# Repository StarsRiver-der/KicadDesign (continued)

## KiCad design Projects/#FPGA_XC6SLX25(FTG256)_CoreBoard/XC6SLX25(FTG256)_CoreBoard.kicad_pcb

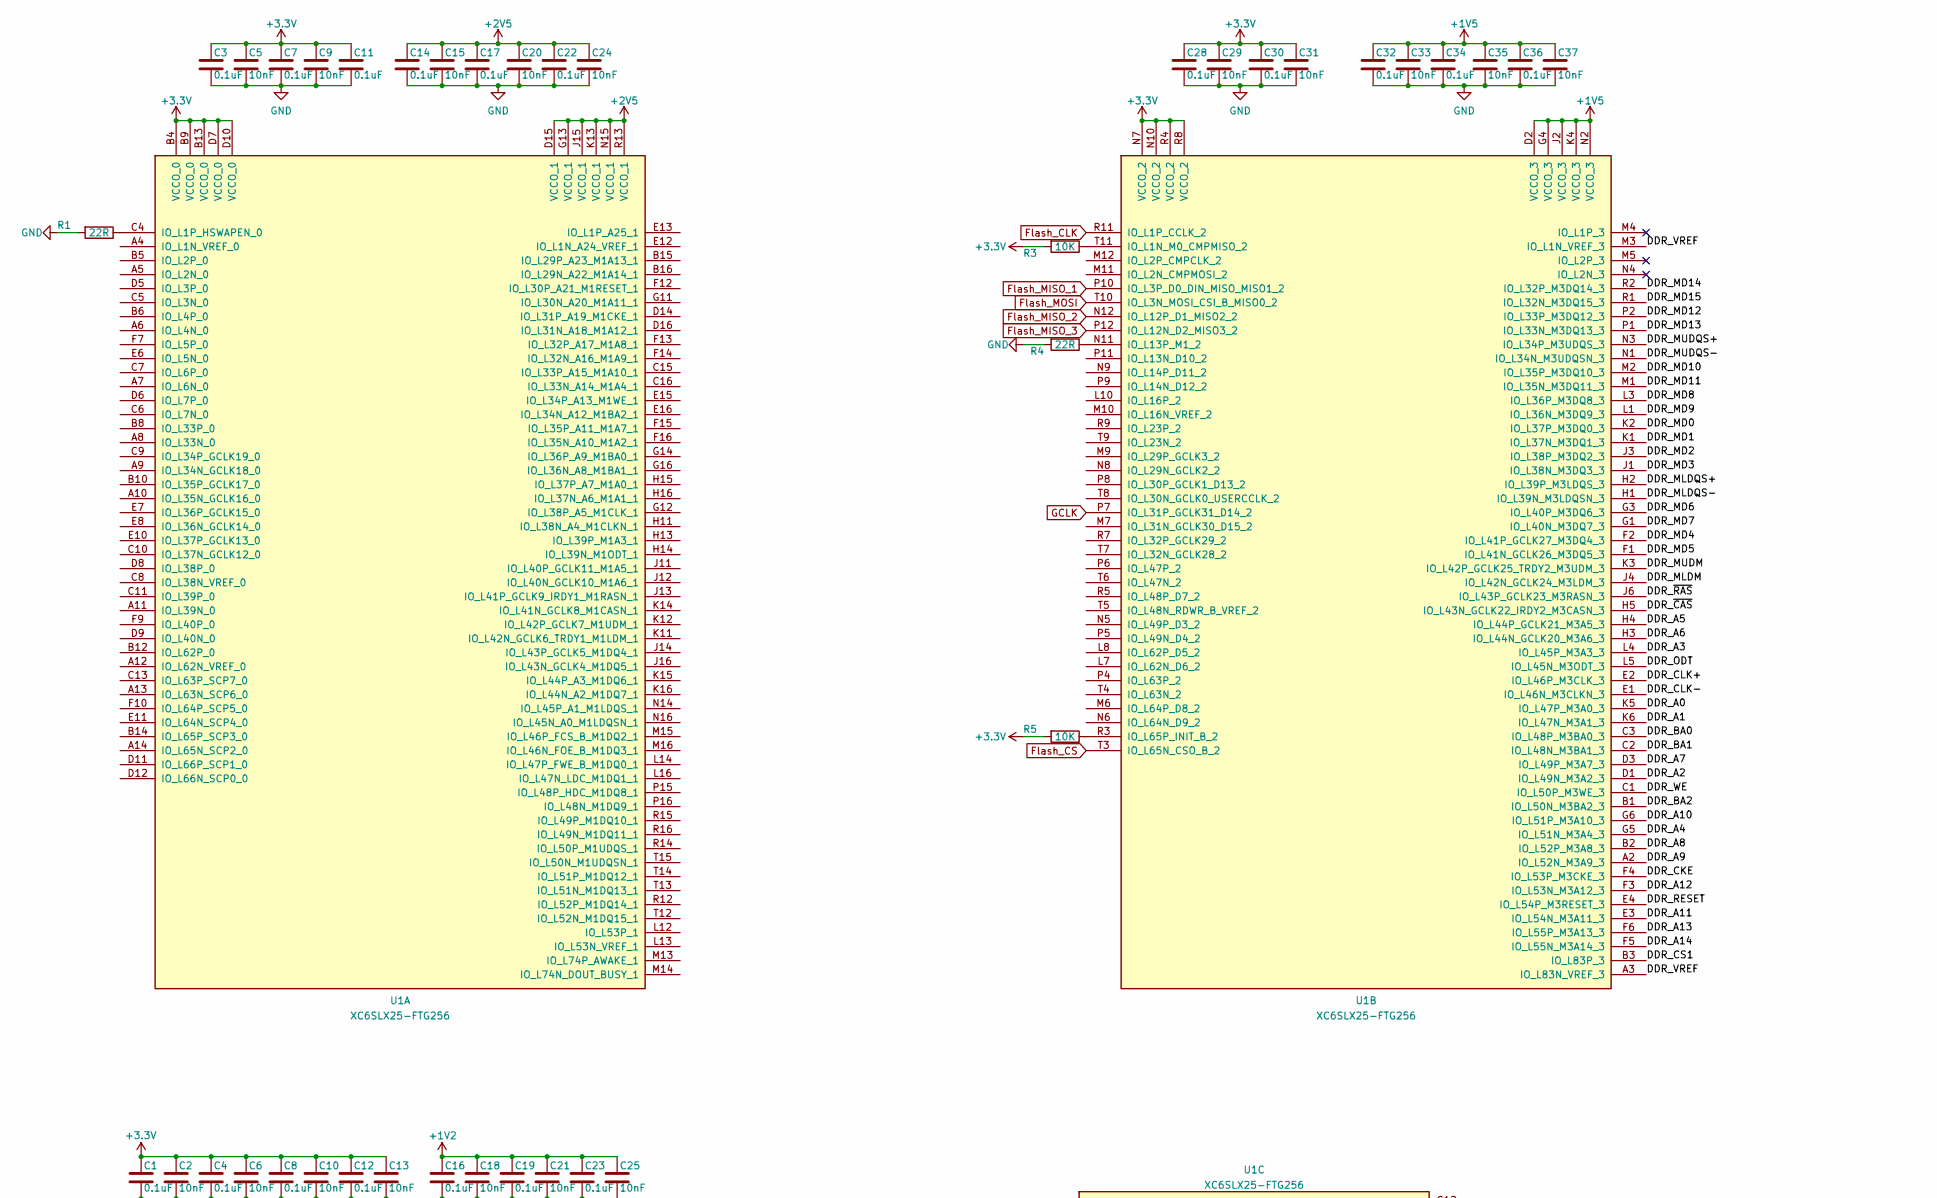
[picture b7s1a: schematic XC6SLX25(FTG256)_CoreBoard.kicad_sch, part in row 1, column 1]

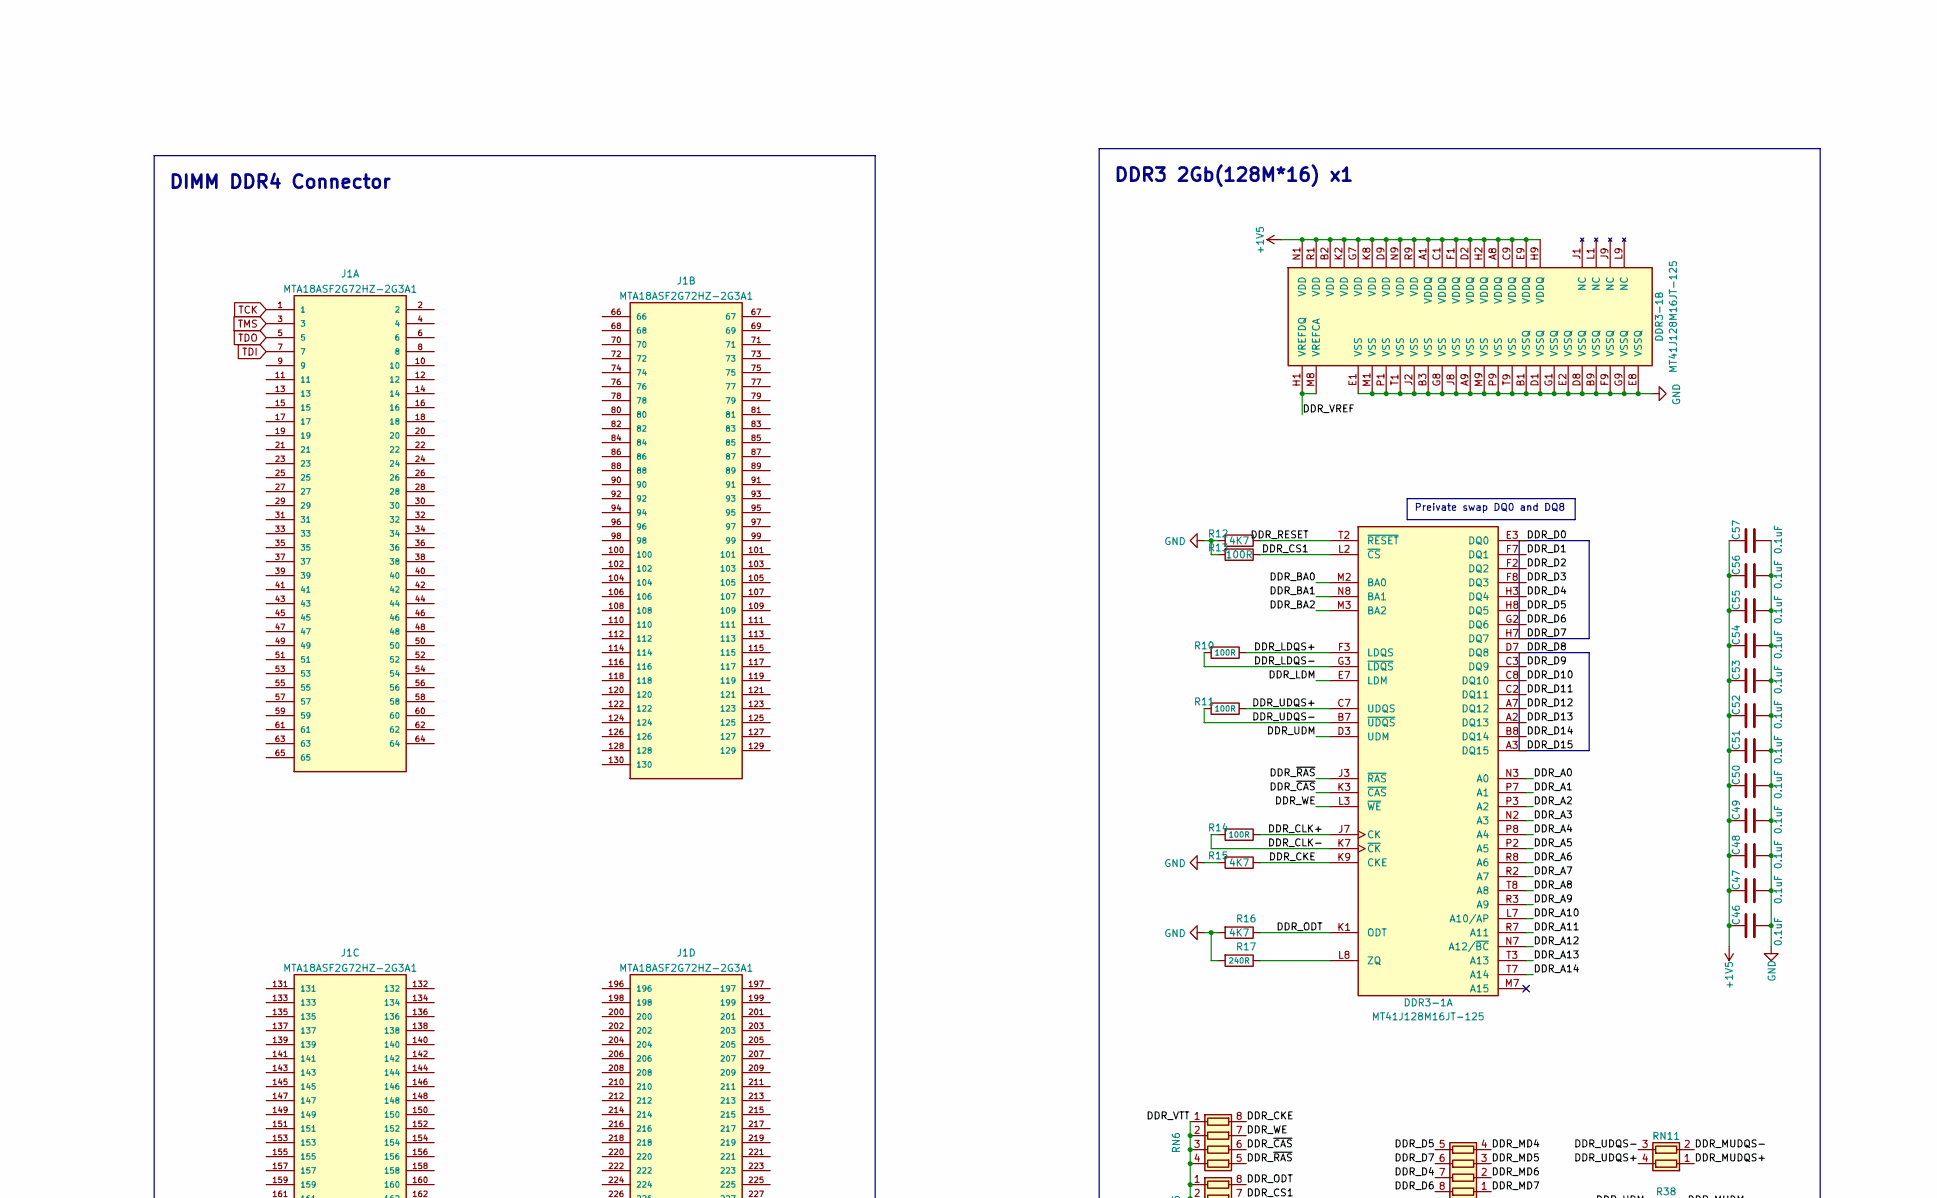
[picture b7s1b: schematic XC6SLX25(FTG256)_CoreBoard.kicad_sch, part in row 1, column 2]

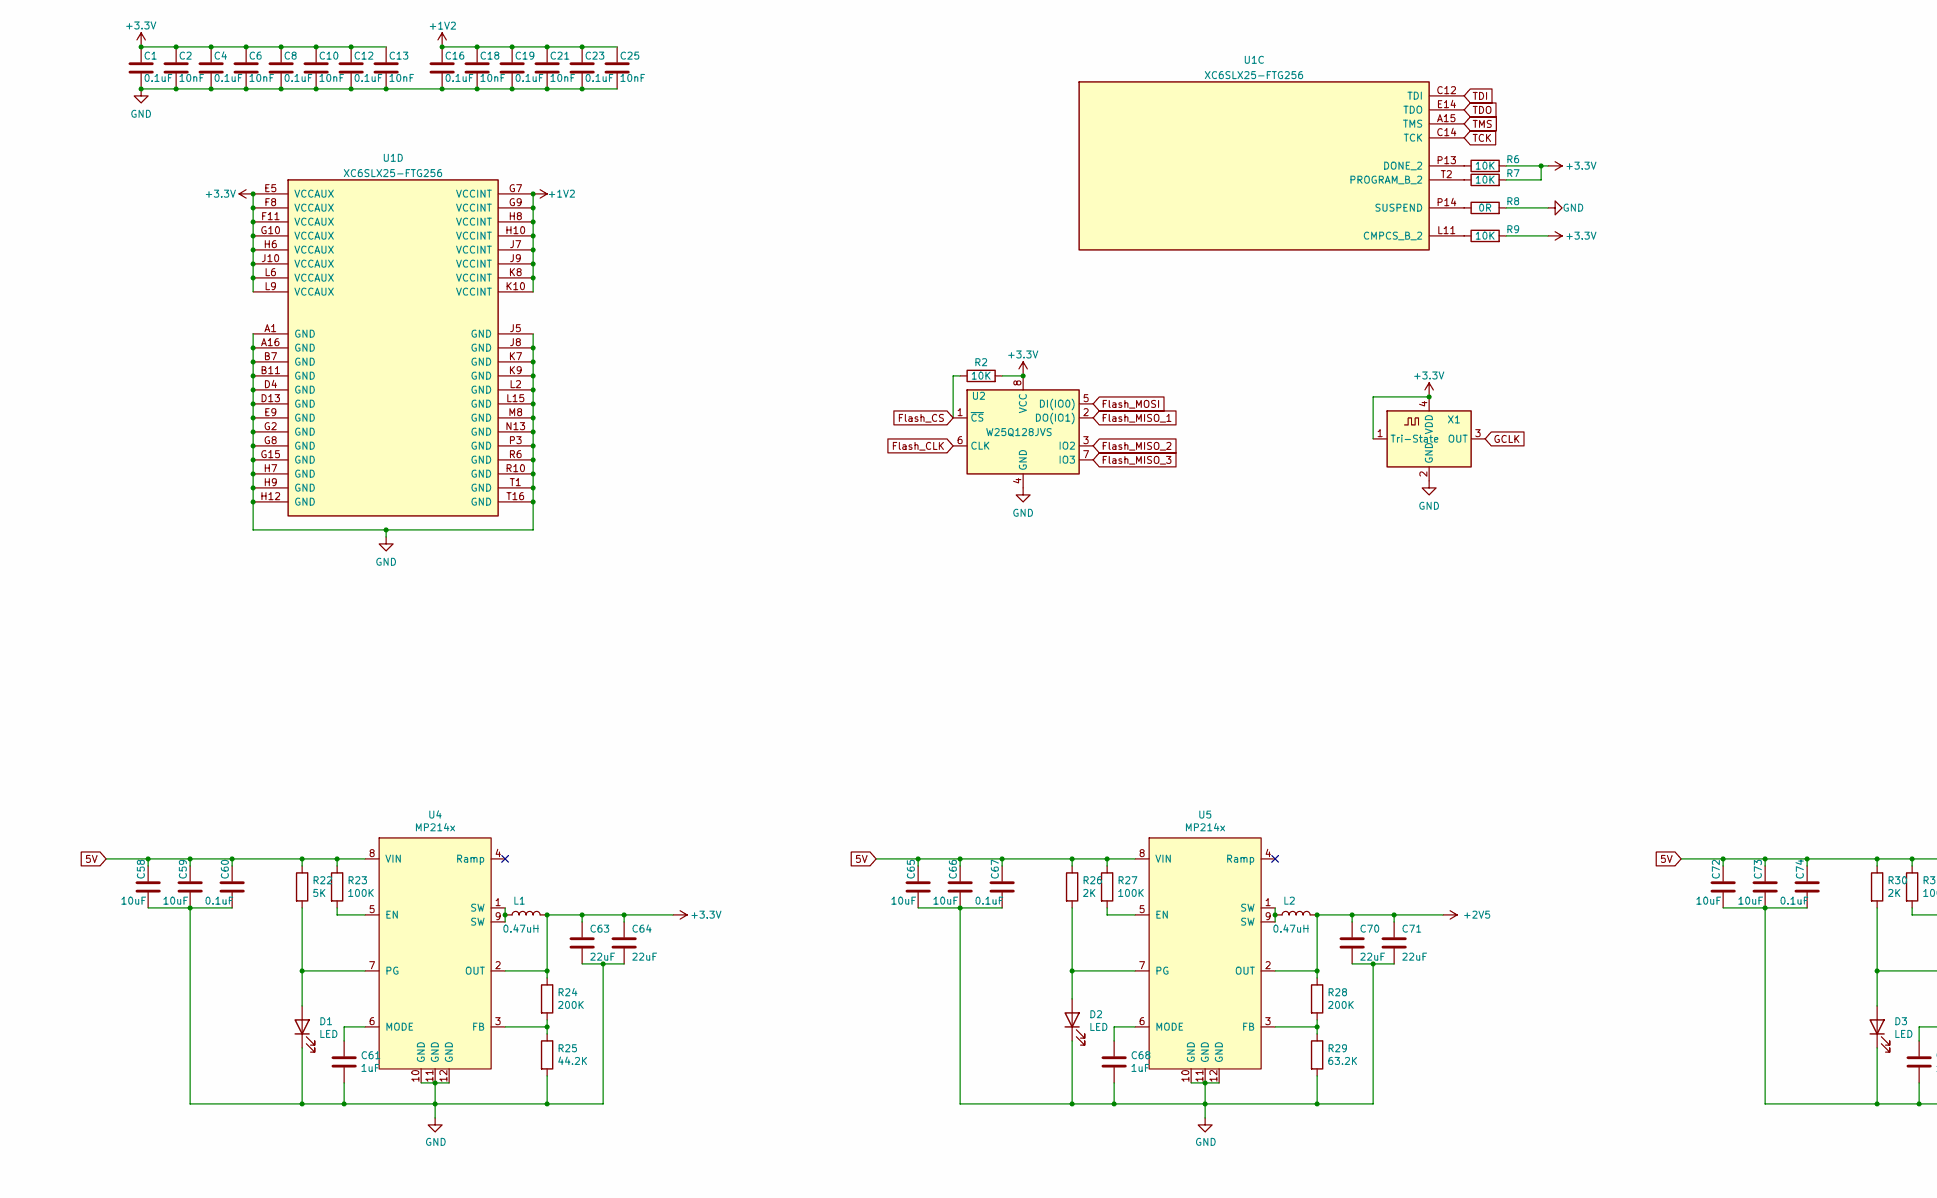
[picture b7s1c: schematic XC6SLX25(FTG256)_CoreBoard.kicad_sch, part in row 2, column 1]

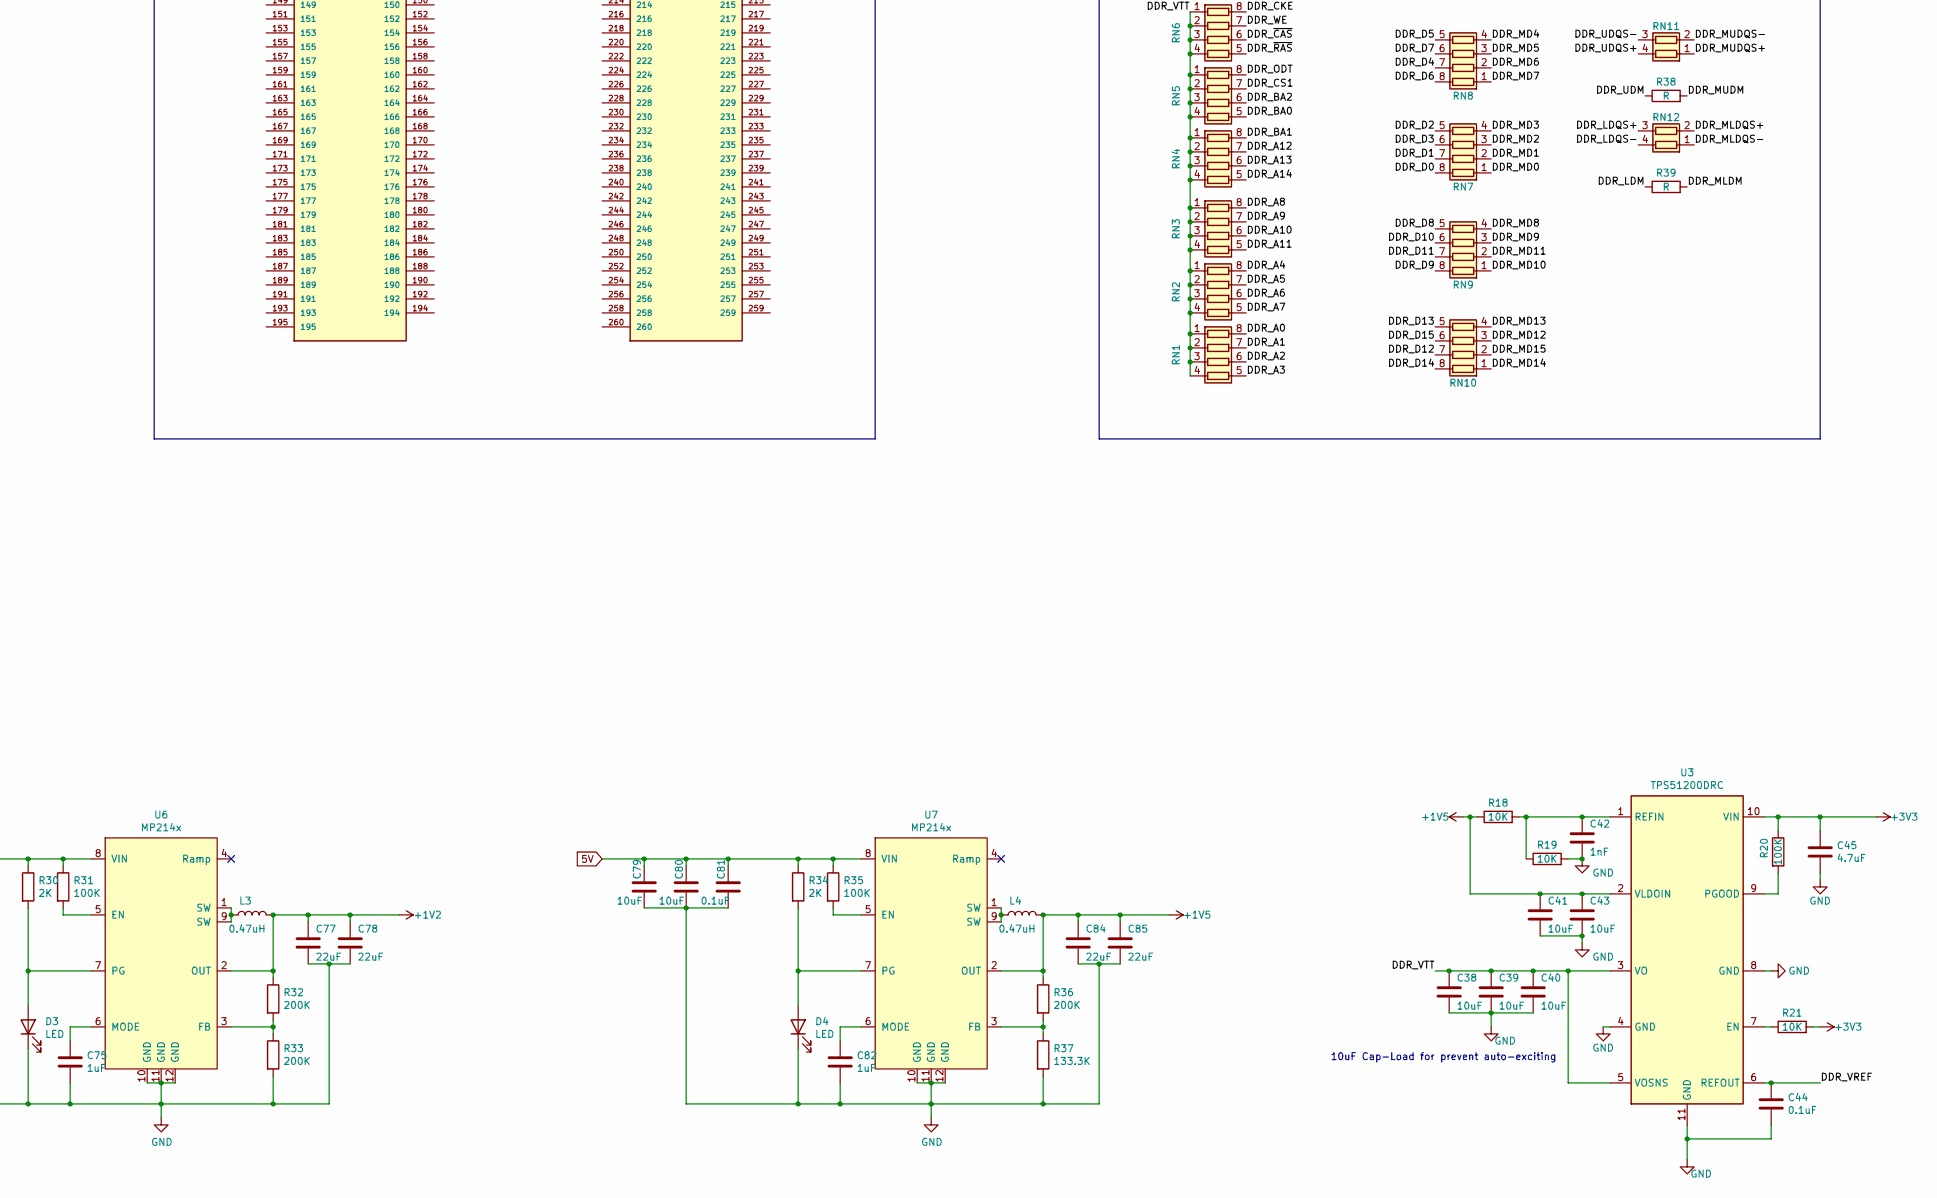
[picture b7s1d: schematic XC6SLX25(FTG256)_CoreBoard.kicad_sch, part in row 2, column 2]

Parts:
C1, C3, C4, C7, C8, C11, C12, C14, C17, C22, C28, C30, C32, C34, C36, C44, C46, C47, C48, C49, C50, C51, C52, C53, C54, C55, C56, C57, C60, C67, C74, C81: 0.1uF; C_0402_1005Metric
C2, C5, C6, C9, C10, C13, C15, C20, C24, C29, C31, C33, C35, C37: 10nF; C_0402_1005Metric
C16, C19, C23: 0.1uF; C_0201_0603Metric
C18, C21, C25: 10nF; C_0201_0603Metric
C38, C39, C40, C41, C43, C58, C59, C65, C66, C72, C73, C79, C80: 10uF; C_0402_1005Metric
C42: 1nF; C_0402_1005Metric
C45: 4.7uF; C_0402_1005Metric
C61, C68, C75, C82: 1uF; C_0402_1005Metric
C63, C64, C70, C71, C77, C78, C84, C85: 22uF; C_0603_1608Metric
D1, D2, D3, D4: LED; LED_0402_1005Metric
DDR3-1: MT41J128M16JT-125; DDR3-BGA96
J1: MTA18ASF2G72HZ-2G3A1; SO-DIMM-DDR4-pcb
L1, L2, L3, L4: 0.47uH; L_Taiyo-Yuden_NR-30xx
R1, R4: 22R; R_0402_1005Metric
R2, R3, R5, R6, R7, R9, R18, R19, R21: 10K; R_0402_1005Metric
R8: 0R; R_0402_1005Metric
R10, R11, R13, R14: 100R; R_0402_1005Metric
R12, R15, R16: 4K7; R_0402_1005Metric
R17: 240R; R_0402_1005Metric
R20, R23, R27, R31, R35: 100K; R_0402_1005Metric
R22: 5K; R_0402_1005Metric
R24, R28, R32, R33, R36: 200K; R_0402_1005Metric
R25: 44.2K; R_0402_1005Metric
R26, R30, R34: 2K; R_0402_1005Metric
R29: 63.2K; R_0402_1005Metric
R37: 133.3K; R_0402_1005Metric
R38, R39: R; R_0402_1005Metric
RN1, RN2, RN3, RN4, RN5, RN6, RN7, RN8, RN9, RN10: R_Pack04; R_Array_Concave_4x0402
RN11, RN12: R_Pack02; R_Array_Convex_2x0402
U1: XC6SLX25-FTG256; Xilinx_FTG256
U2: W25Q128JVS; SOIC-8_5.23x5.23mm_P1.27mm
U3: TPS51200DRC; VSON-10-1EP_3x3mm_P0.5mm_EP1.65x2.4mm
U4, U5, U6, U7: MP214x; MP2145
X1: ECS-2520MV-xxx-xx; Oscillator_SMD_ECS_2520MV-xxx-xx-4Pin_2.5x2.0mm

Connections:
5V: C58.1, C59.1, C60.1, C65.1, C66.1, C67.1, C72.1, C73.1, C74.1, C79.1, C80.1, C81.1, R22.1, R23.1, R26.1, R27.1, R30.1, R31.1, R34.1, R35.1, U4.8 (VIN), U5.8 (VIN), U6.8 (VIN), U7.8 (VIN)
+1V2: C16.1, C18.1, C19.1, C21.1, C23.1, C25.1, C77.1, C78.1, L3.2, R32.1, U1.G7 (VCCINT), U1.G9 (VCCINT), U1.H8 (VCCINT), U1.H10 (VCCINT), U1.J7 (VCCINT), U1.J9 (VCCINT), U1.K8 (VCCINT), U1.K10 (VCCINT), U6.2 (OUT)
+1V5: C32.1, C33.1, C34.1, C35.1, C36.1, C37.1, C41.1, C43.1, C46.1, C47.1, C48.1, C49.1, C50.1, C51.1, C52.1, C53.1, C54.1, C55.1, C56.1, C57.1, C84.1, C85.1, DDR3-1.A1 (VDDQ), DDR3-1.A8 (VDDQ), DDR3-1.B2 (VDD), DDR3-1.C1 (VDDQ), DDR3-1.C9 (VDDQ), DDR3-1.D2 (VDDQ), DDR3-1.D9 (VDD), DDR3-1.E9 (VDDQ), DDR3-1.F1 (VDDQ), DDR3-1.G7 (VDD), DDR3-1.H2 (VDDQ), DDR3-1.H9 (VDDQ), DDR3-1.K2 (VDD), DDR3-1.K8 (VDD), DDR3-1.N1 (VDD), DDR3-1.N9 (VDD), DDR3-1.R1 (VDD), DDR3-1.R9 (VDD), L4.2, R18.1, R36.1, U1.D2 (VCCO_3), U1.G4 (VCCO_3), U1.J2 (VCCO_3), U1.K4 (VCCO_3), U1.N2 (VCCO_3), U3.2 (VLDOIN), U7.2 (OUT)
+2V5: C14.1, C15.1, C17.1, C20.1, C22.1, C24.1, C70.1, C71.1, L2.2, R28.1, U1.D15 (VCCO_1), U1.G13 (VCCO_1), U1.J15 (VCCO_1), U1.K13 (VCCO_1), U1.N15 (VCCO_1), U1.R13 (VCCO_1), U5.2 (OUT)
/DDR_A0: DDR3-1.N3 (A0), RN1.8 (R1.2), U1.K5 (IO_L47P_M3A0_3)
/DDR_A1: DDR3-1.P7 (A1), RN1.7 (R2.2), U1.K6 (IO_L47N_M3A1_3)
/DDR_A2: DDR3-1.P3 (A2), RN1.6 (R3.2), U1.D1 (IO_L49N_M3A2_3)
/DDR_A3: DDR3-1.N2 (A3), RN1.5 (R4.2), U1.L4 (IO_L45P_M3A3_3)
/DDR_A4: DDR3-1.P8 (A4), RN2.8 (R1.2), U1.G5 (IO_L51N_M3A4_3)
/DDR_A5: DDR3-1.P2 (A5), RN2.7 (R2.2), U1.H4 (IO_L44P_GCLK21_M3A5_3)
/DDR_A6: DDR3-1.R8 (A6), RN2.6 (R3.2), U1.H3 (IO_L44N_GCLK20_M3A6_3)
/DDR_A7: DDR3-1.R2 (A7), RN2.5 (R4.2), U1.D3 (IO_L49P_M3A7_3)
/DDR_A8: DDR3-1.T8 (A8), RN3.8 (R1.2), U1.B2 (IO_L52P_M3A8_3)
/DDR_A9: DDR3-1.R3 (A9), RN3.7 (R2.2), U1.A2 (IO_L52N_M3A9_3)
/DDR_A10: DDR3-1.L7 (A10/AP), RN3.6 (R3.2), U1.G6 (IO_L51P_M3A10_3)
/DDR_A11: DDR3-1.R7 (A11), RN3.5 (R4.2), U1.E3 (IO_L54N_M3A11_3)
/DDR_A12: DDR3-1.N7 (A12/~BC), RN4.7 (R2.2), U1.F3 (IO_L53N_M3A12_3)
/DDR_A13: DDR3-1.T3 (A13), RN4.6 (R3.2), U1.F6 (IO_L55P_M3A13_3)
/DDR_A14: DDR3-1.T7 (A14), RN4.5 (R4.2), U1.F5 (IO_L55N_M3A14_3)
/DDR_BA0: DDR3-1.M2 (BA0), RN5.5 (R4.2), U1.C3 (IO_L48P_M3BA0_3)
/DDR_BA1: DDR3-1.N8 (BA1), RN4.8 (R1.2), U1.C2 (IO_L48N_M3BA1_3)
/DDR_BA2: DDR3-1.M3 (BA2), RN5.6 (R3.2), U1.B1 (IO_L50N_M3BA2_3)
/DDR_CKE: DDR3-1.K9 (CKE), R15.1, RN6.8 (R1.2), U1.F4 (IO_L53P_M3CKE_3)
/DDR_CLK+: DDR3-1.J7 (CK), R14.1, U1.E2 (IO_L46P_M3CLK_3)
/DDR_CLK-: DDR3-1.K7 (~CK), R14.2, U1.E1 (IO_L46N_M3CLKN_3)
/DDR_CS1: DDR3-1.L2 (~CS), R13.1, RN5.7 (R2.2), U1.B3 (IO_L83P_3)
/DDR_D0: DDR3-1.E3 (DQ0), RN7.8 (R1.2)
/DDR_D1: DDR3-1.F7 (DQ1), RN7.7 (R2.2)
/DDR_D2: DDR3-1.F2 (DQ2), RN7.5 (R4.2)
/DDR_D3: DDR3-1.F8 (DQ3), RN7.6 (R3.2)
/DDR_D4: DDR3-1.H3 (DQ4), RN8.7 (R2.2)
/DDR_D5: DDR3-1.H8 (DQ5), RN8.5 (R4.2)
/DDR_D6: DDR3-1.G2 (DQ6), RN8.8 (R1.2)
/DDR_D7: DDR3-1.H7 (DQ7), RN8.6 (R3.2)
/DDR_D8: DDR3-1.D7 (DQ8), RN9.5 (R4.2)
/DDR_D9: DDR3-1.C3 (DQ9), RN9.8 (R1.2)
/DDR_D10: DDR3-1.C8 (DQ10), RN9.6 (R3.2)
/DDR_D11: DDR3-1.C2 (DQ11), RN9.7 (R2.2)
/DDR_D12: DDR3-1.A7 (DQ12), RN10.7 (R2.2)
/DDR_D13: DDR3-1.A2 (DQ13), RN10.5 (R4.2)
/DDR_D14: DDR3-1.B8 (DQ14), RN10.8 (R1.2)
/DDR_D15: DDR3-1.A3 (DQ15), RN10.6 (R3.2)
/DDR_LDM: DDR3-1.E7 (LDM), R39.1
/DDR_LDQS+: DDR3-1.F3 (LDQS), R10.1, RN12.3 (R2.2)
/DDR_LDQS-: DDR3-1.G3 (~LDQS), R10.2, RN12.4 (R1.2)
/DDR_MD0: RN7.1 (R1.1), U1.K2 (IO_L37P_M3DQ0_3)
/DDR_MD1: RN7.2 (R2.1), U1.K1 (IO_L37N_M3DQ1_3)
/DDR_MD2: RN7.3 (R3.1), U1.J3 (IO_L38P_M3DQ2_3)
/DDR_MD3: RN7.4 (R4.1), U1.J1 (IO_L38N_M3DQ3_3)
/DDR_MD4: RN8.4 (R4.1), U1.F2 (IO_L41P_GCLK27_M3DQ4_3)
/DDR_MD5: RN8.3 (R3.1), U1.F1 (IO_L41N_GCLK26_M3DQ5_3)
/DDR_MD6: RN8.2 (R2.1), U1.G3 (IO_L40P_M3DQ6_3)
/DDR_MD7: RN8.1 (R1.1), U1.G1 (IO_L40N_M3DQ7_3)
/DDR_MD8: RN9.4 (R4.1), U1.L3 (IO_L36P_M3DQ8_3)
/DDR_MD9: RN9.3 (R3.1), U1.L1 (IO_L36N_M3DQ9_3)
/DDR_MD10: RN9.1 (R1.1), U1.M2 (IO_L35P_M3DQ10_3)
/DDR_MD11: RN9.2 (R2.1), U1.M1 (IO_L35N_M3DQ11_3)
/DDR_MD12: RN10.3 (R3.1), U1.P2 (IO_L33P_M3DQ12_3)
/DDR_MD13: RN10.4 (R4.1), U1.P1 (IO_L33N_M3DQ13_3)
/DDR_MD14: RN10.1 (R1.1), U1.R2 (IO_L32P_M3DQ14_3)
/DDR_MD15: RN10.2 (R2.1), U1.R1 (IO_L32N_M3DQ15_3)
/DDR_MLDM: R39.2, U1.J4 (IO_L42N_GCLK24_M3LDM_3)
/DDR_MLDQS+: RN12.2 (R2.1), U1.H2 (IO_L39P_M3LDQS_3)
/DDR_MLDQS-: RN12.1 (R1.1), U1.H1 (IO_L39N_M3LDQSN_3)
/DDR_MUDM: R38.2, U1.K3 (IO_L42P_GCLK25_TRDY2_M3UDM_3)
/DDR_MUDQS+: RN11.1 (R1.1), U1.N3 (IO_L34P_M3UDQS_3)
/DDR_MUDQS-: RN11.2 (R2.1), U1.N1 (IO_L34N_M3UDQSN_3)
/DDR_ODT: DDR3-1.K1 (ODT), R16.1, RN5.8 (R1.2), U1.L5 (IO_L45N_M3ODT_3)
/DDR_RESET: DDR3-1.T2 (~RESET), R12.1, U1.E4 (IO_L54P_M3RESET_3)
/DDR_UDM: DDR3-1.D3 (UDM), R38.1
/DDR_UDQS+: DDR3-1.C7 (UDQS), R11.1, RN11.4 (R1.2)
/DDR_UDQS-: DDR3-1.B7 (~UDQS), R11.2, RN11.3 (R2.2)
/DDR_VREF: C44.1, DDR3-1.H1 (VREFDQ), DDR3-1.M8 (VREFCA), U1.A3 (IO_L83N_VREF_3), U1.M3 (IO_L1N_VREF_3), U3.6 (REFOUT)
/DDR_VTT: C38.1, C39.1, C40.1, RN1.1 (R1.1), RN1.2 (R2.1), RN1.3 (R3.1), RN1.4 (R4.1), RN2.1 (R1.1), RN2.2 (R2.1), RN2.3 (R3.1), RN2.4 (R4.1), RN3.1 (R1.1), RN3.2 (R2.1), RN3.3 (R3.1), RN3.4 (R4.1), RN4.1 (R1.1), RN4.2 (R2.1), RN4.3 (R3.1), RN4.4 (R4.1), RN5.1 (R1.1), RN5.2 (R2.1), RN5.3 (R3.1), RN5.4 (R4.1), RN6.1 (R1.1), RN6.2 (R2.1), RN6.3 (R3.1), RN6.4 (R4.1), U3.3 (VO), U3.5 (VOSNS)
/DDR_WE: DDR3-1.L3 (~WE), RN6.7 (R2.2), U1.C1 (IO_L50P_M3WE_3)
/DDR_~CAS: DDR3-1.K3 (~CAS), RN6.6 (R3.2), U1.H5 (IO_L43N_GCLK22_IRDY2_M3CASN_3)
/DDR_~RAS: DDR3-1.J3 (~RAS), RN6.5 (R4.2), U1.J6 (IO_L43P_GCLK23_M3RASN_3)
Flash_CLK: U1.R11 (IO_L1P_CCLK_2), U2.6 (CLK)
Flash_CS: R2.1, U1.T3 (IO_L65N_CSO_B_2), U2.1 (~CS)
Flash_MISO_1: U1.P10 (IO_L3P_D0_DIN_MISO_MISO1_2), U2.2 (DO(IO1))
Flash_MISO_2: U1.N12 (IO_L12P_D1_MISO2_2), U2.3 (IO2)
Flash_MISO_3: U1.P12 (IO_L12N_D2_MISO3_2), U2.7 (IO3)
Flash_MOSI: U1.T10 (IO_L3N_MOSI_CSI_B_MISO0_2), U2.5 (DI(IO0))
GCLK: U1.P7 (IO_L31P_GCLK31_D14_2), X1.3 (OUT)
GND: C1.2, C2.2, C3.2, C4.2, C5.2, C6.2, C7.2, C8.2, C9.2, C10.2, C11.2, C12.2, C13.2, C14.2, C15.2, C16.2, C17.2, C18.2, C19.2, C20.2, C21.2, C22.2, C23.2, C24.2, C25.2, C28.2, C29.2, C30.2, C31.2, C32.2, C33.2, C34.2, C35.2, C36.2, C37.2, C38.2, C39.2, C40.2, C41.2, C42.2, C43.2, C44.2, C45.2, C46.2, C47.2, C48.2, C49.2, C50.2, C51.2, C52.2, C53.2, C54.2, C55.2, C56.2, C57.2, C58.2, C59.2, C60.2, C61.2, C63.2, C64.2, C65.2, C66.2, C67.2, C68.2, C70.2, C71.2, C72.2, C73.2, C74.2, C75.2, C77.2, C78.2, C79.2, C80.2, C81.2, C82.2, C84.2, C85.2, D1.1 (K), D2.1 (K), D3.1 (K), D4.1 (K), DDR3-1.A9 (VSS), DDR3-1.B1 (VSSQ), DDR3-1.B3 (VSS), DDR3-1.B9 (VSSQ), DDR3-1.D1 (VSSQ), DDR3-1.D8 (VSSQ), DDR3-1.E1 (VSS), DDR3-1.E2 (VSSQ), DDR3-1.E8 (VSSQ), DDR3-1.F9 (VSSQ), DDR3-1.G1 (VSSQ), DDR3-1.G8 (VSS), DDR3-1.G9 (VSSQ), DDR3-1.J2 (VSS), DDR3-1.J8 (VSS), DDR3-1.M1 (VSS), DDR3-1.M9 (VSS), DDR3-1.P1 (VSS), DDR3-1.P9 (VSS), DDR3-1.T1 (VSS), DDR3-1.T9 (VSS), R1.2, R4.2, R8.2, R12.2, R13.2, R15.2, R16.2, R17.2, R19.2, R25.2, R29.2, R33.2, R37.2, U1.A1 (GND), U1.A16 (GND), U1.B7 (GND), U1.B11 (GND), U1.D4 (GND), U1.D13 (GND), U1.E9 (GND), U1.G2 (GND), U1.G8 (GND), U1.G15 (GND), U1.H7 (GND), U1.H9 (GND), U1.H12 (GND), U1.J5 (GND), U1.J8 (GND), U1.K7 (GND), U1.K9 (GND), U1.L2 (GND), U1.L15 (GND), U1.M8 (GND), U1.N13 (GND), U1.P3 (GND), U1.R6 (GND), U1.R10 (GND), U1.T1 (GND), U1.T16 (GND), U2.4 (GND), U3.4 (GND), U3.8 (GND), U3.11 (GND), U4.10 (GND), U4.11 (GND), U4.12 (GND), U5.10 (GND)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
unnamed: C42.1, R18.2, R19.1, U3.1 (REFIN)
unnamed: C61.1, U4.6 (MODE)
unnamed: C68.1, U5.6 (MODE)
unnamed: C75.1, U6.6 (MODE)
unnamed: C82.1, U7.6 (MODE)
unnamed: D1.2 (A), R22.2, U4.7 (PG)
unnamed: D2.2 (A), R26.2, U5.7 (PG)
unnamed: D3.2 (A), R30.2, U6.7 (PG)
unnamed: D4.2 (A), R34.2, U7.7 (PG)
unnamed: DDR3-1.L8 (ZQ), R17.1
unnamed: L1.1, U4.1 (SW), U4.9 (SW)
unnamed: L2.1, U5.1 (SW), U5.9 (SW)
unnamed: L3.1, U6.1 (SW), U6.9 (SW)
unnamed: L4.1, U7.1 (SW), U7.9 (SW)
unnamed: R1.1, U1.C4 (IO_L1P_HSWAPEN_0)
unnamed: R3.1, U1.T11 (IO_L1N_M0_CMPMISO_2)
unnamed: R4.1, U1.N11 (IO_L13P_M1_2)
unnamed: R5.1, U1.R3 (IO_L65P_INIT_B_2)
unnamed: R6.1, U1.P13 (DONE_2)
unnamed: R7.1, U1.T2 (PROGRAM_B_2)
unnamed: R8.1, U1.P14 (SUSPEND)
unnamed: R9.1, U1.L11 (CMPCS_B_2)
unnamed: R20.2, U3.9 (PGOOD)
unnamed: R21.1, U3.7 (EN)
unnamed: R23.2, U4.5 (EN)
unnamed: R24.2, R25.1, U4.3 (FB)
unnamed: R27.2, U5.5 (EN)
unnamed: R28.2, R29.1, U5.3 (FB)
unnamed: R31.2, U6.5 (EN)
unnamed: R32.2, R33.1, U6.3 (FB)
unnamed: R35.2, U7.5 (EN)
unnamed: R36.2, R37.1, U7.3 (FB)
TCK: J1.1, U1.C14 (TCK)
TDI: J1.7, U1.C12 (TDI)
TDO: J1.5, U1.E14 (TDO)
TMS: J1.3, U1.A15 (TMS)

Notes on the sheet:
10uF Cap-Load for prevent auto-exciting
DDR3 2Gb(128M*16) x1
DIMM DDR4 Connector
Preivate swap DQ0 and DQ8

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
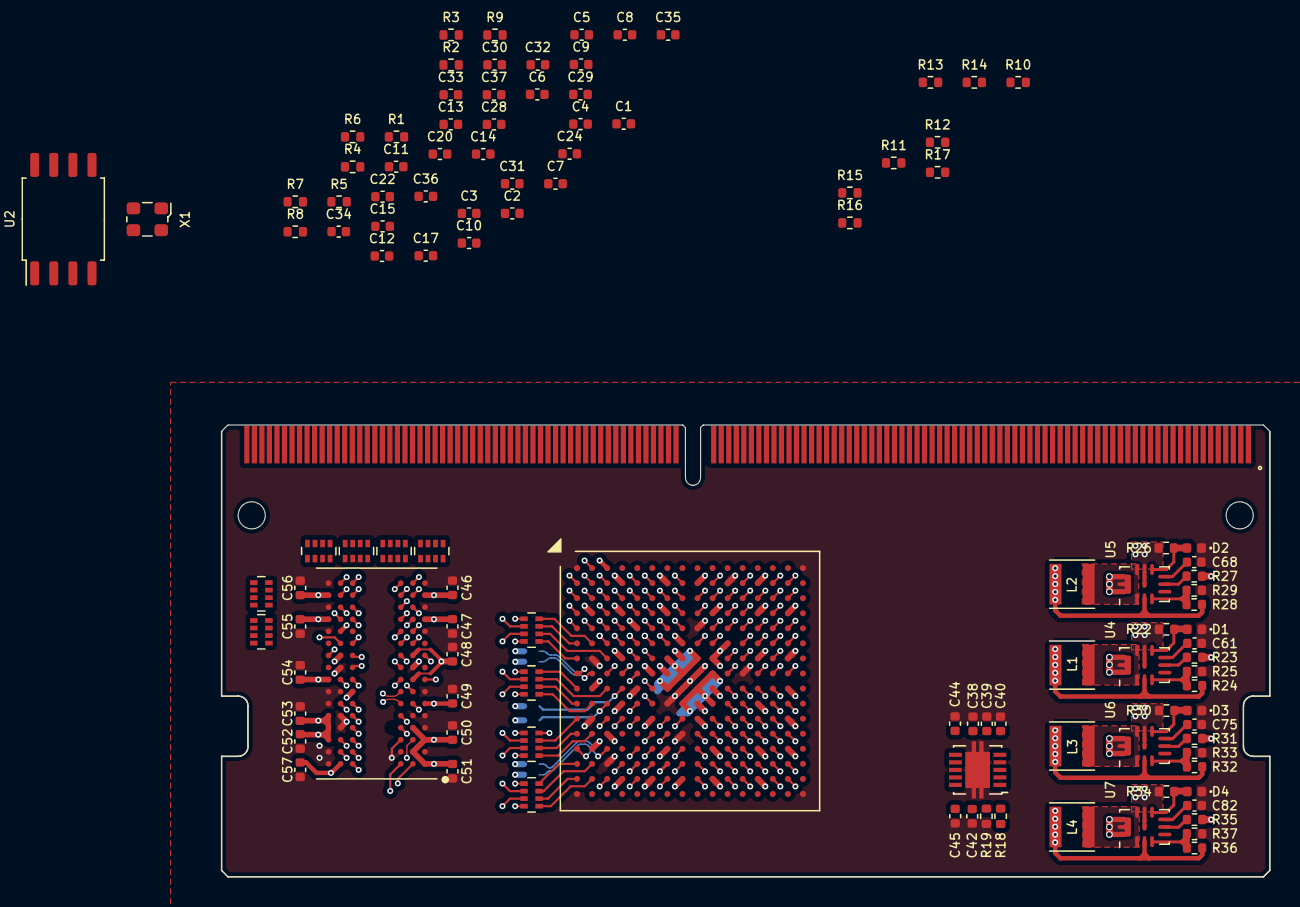
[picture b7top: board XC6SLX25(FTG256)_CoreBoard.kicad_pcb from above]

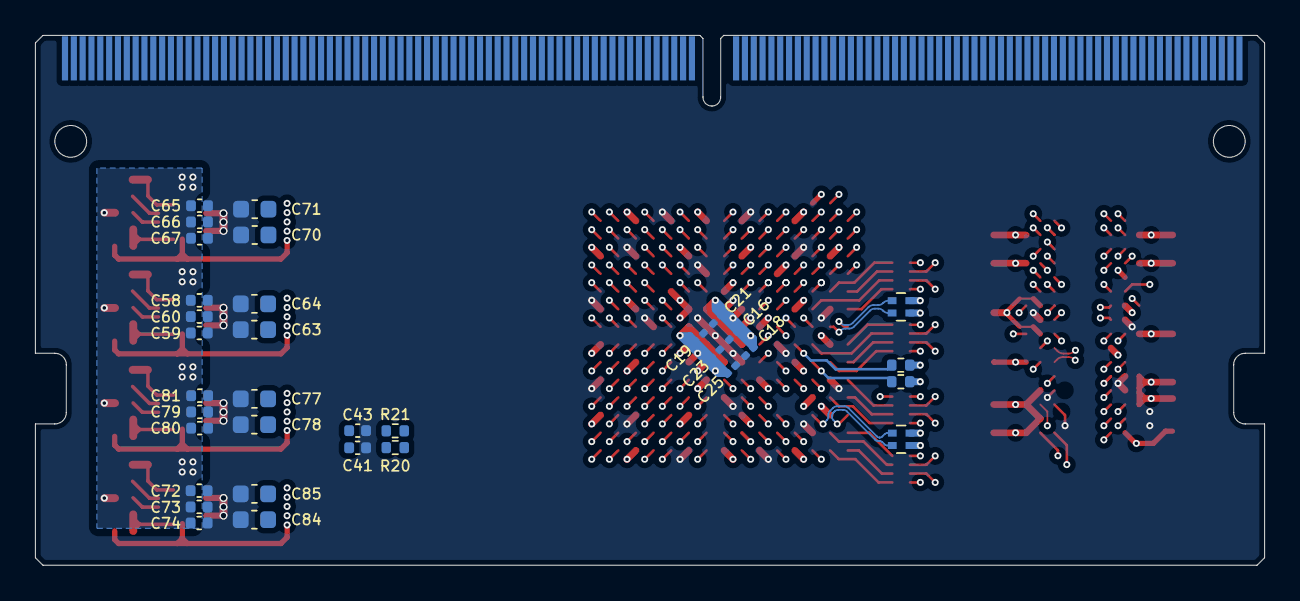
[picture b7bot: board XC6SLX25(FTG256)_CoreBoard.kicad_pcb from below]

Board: 6 copper layers, 69.6 x 30.0 mm, 148 parts (34 on the bottom side), 122 nets.

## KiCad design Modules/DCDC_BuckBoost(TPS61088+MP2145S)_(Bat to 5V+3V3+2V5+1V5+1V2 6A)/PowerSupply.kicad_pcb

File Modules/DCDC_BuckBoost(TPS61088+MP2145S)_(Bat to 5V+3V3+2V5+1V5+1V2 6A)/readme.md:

# 2.8V-4.2V 锂电池输入的 DCDC 单极性多轨电源
* 工作温度：0-85℃
* 5V、3v3、2v5、1v5、1v2多轨输出
* 最高30W输出

# 注意事项
* 使用Kicad6绘制

# 原理
见说明手册

# 接口
* 电压输入和控制输入：FPC_Hirose_FH12-14S
* 电压输出和控制输出：PCI_1x

# 预览
_(Bat%20to%205V+3V3+2V5+1V5+1V2%206A)/preview.jpg)

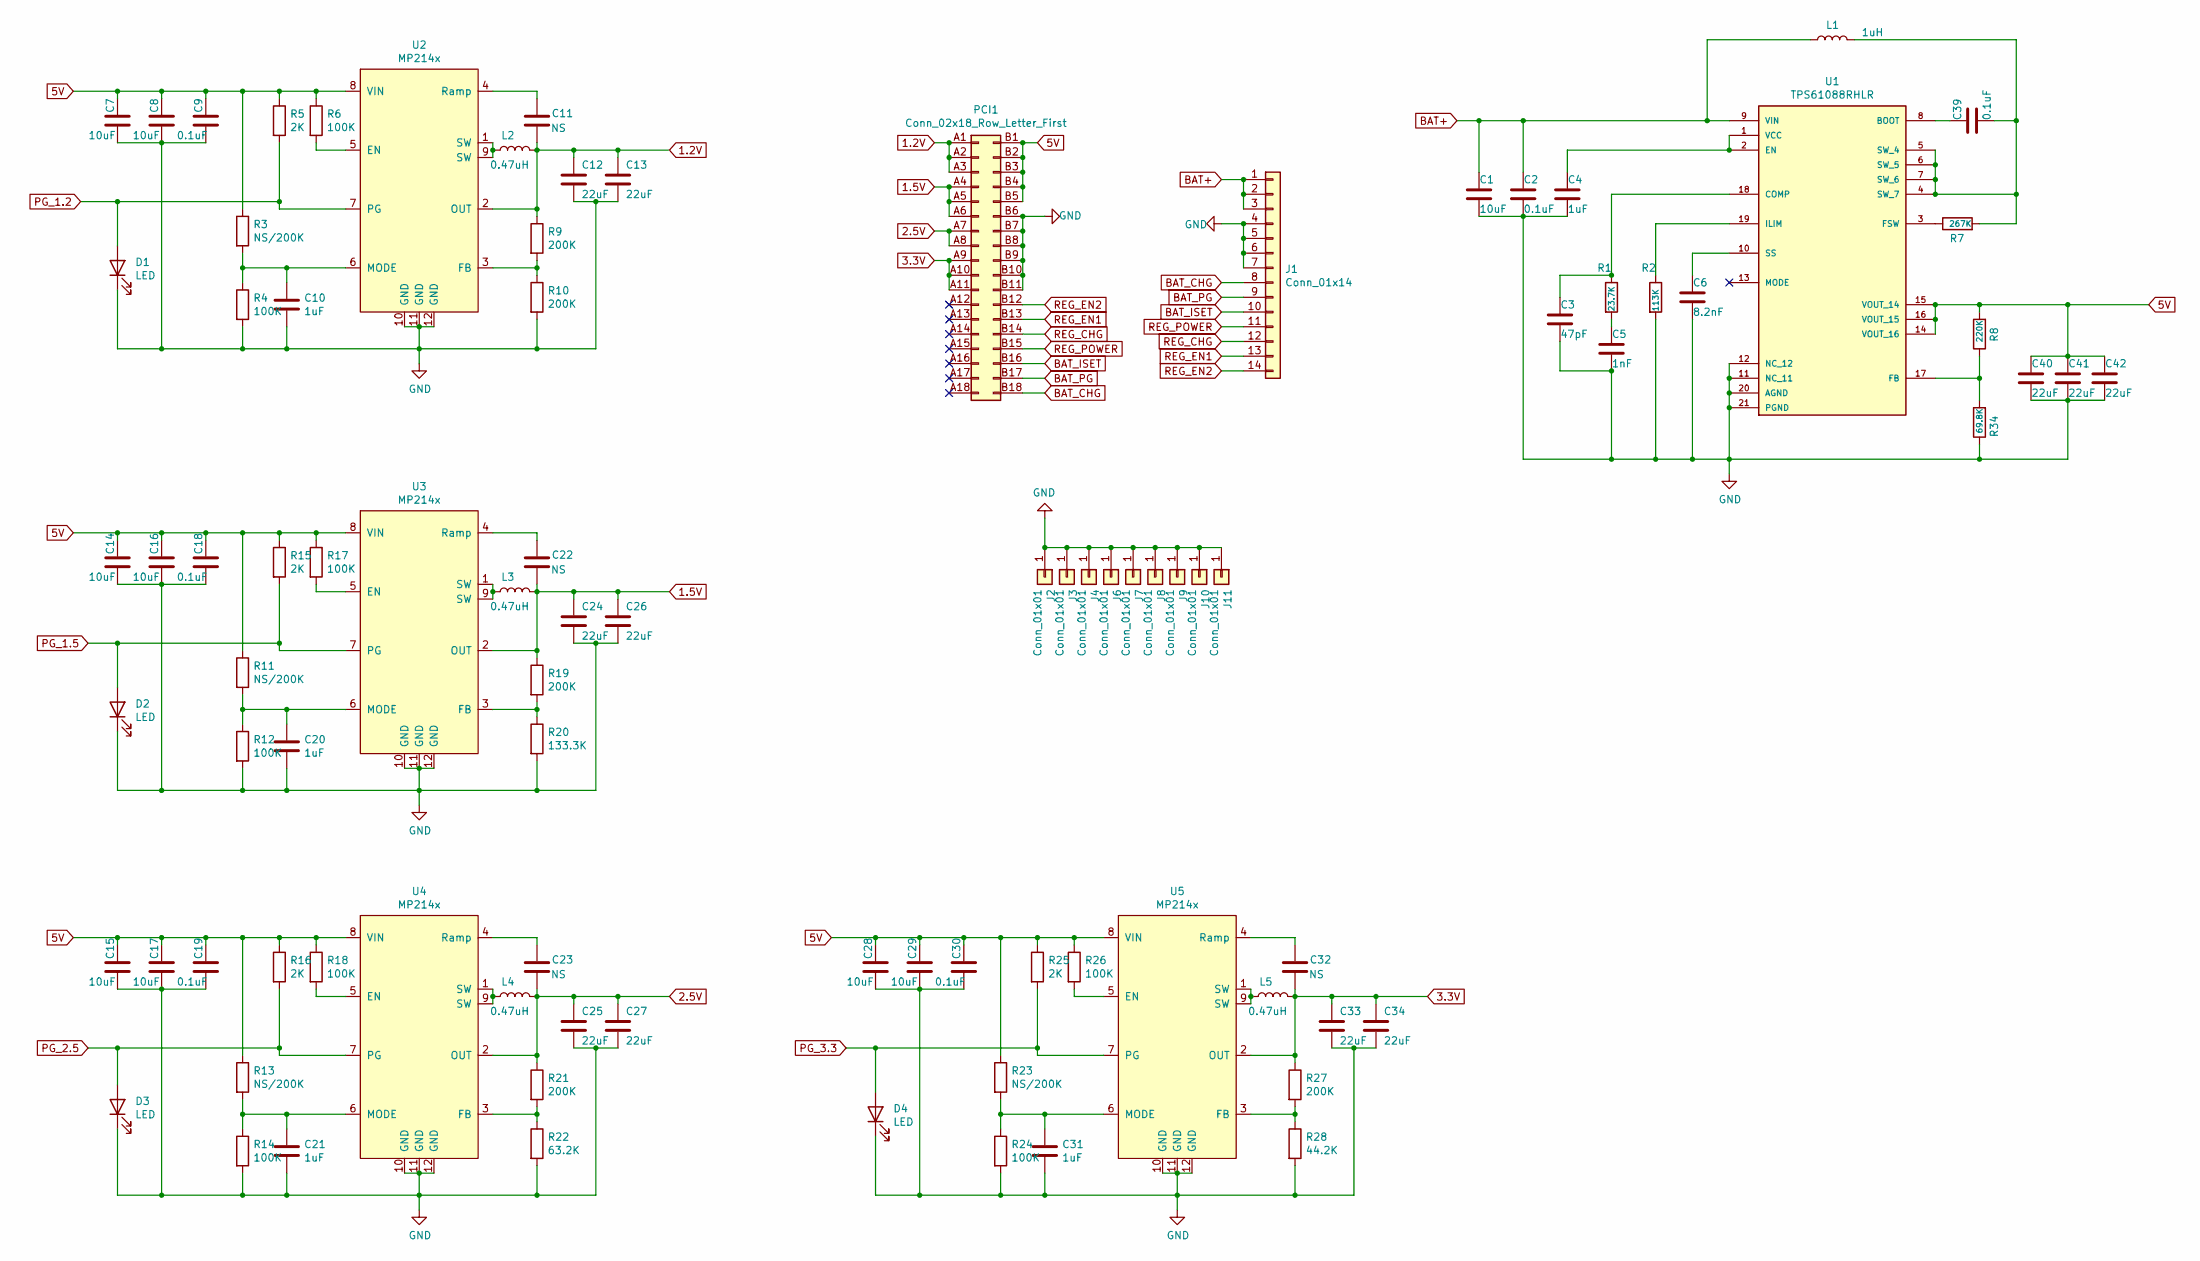
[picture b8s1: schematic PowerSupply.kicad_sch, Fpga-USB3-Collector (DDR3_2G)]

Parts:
C1, C7, C8, C14, C15, C16, C17, C28, C29: 10uF; C_0603_1608Metric
C2, C9, C18, C19, C30, C39: 0.1uF; C_0402_1005Metric
C3: 47pF; C_0402_1005Metric
C4, C10, C20, C21, C31: 1uF; C_0402_1005Metric
C5: 1nF; C_0402_1005Metric
C6: 8.2nF; C_0402_1005Metric
C11, C22, C23, C32: NS; C_0402_1005Metric
C12, C13, C24, C25, C26, C27, C33, C34, C40, C41, C42: 22uF; C_0603_1608Metric
D1, D2, D3, D4: LED; LED_0402_1005Metric
J1: Conn_01x14; Hirose_FH12-14S-0.5SH_1x14-1MP_P0.50mm_Horizontal
J2, J3, J4, J6, J7, J8, J9, J10, J11: Conn_01x01; pad-6-1.5
L1: 1uH; L_Sunlord_MWSA0518_5.4x5.2mm
L2, L3, L4, L5: 0.47uH; L_Sunlord_MWSA0518_5.4x5.2mm
PCI1: Conn_02x18_Row_Letter_First; BUS_PCIexpress_x1
R1: 23.7K; R_0402_1005Metric
R2: 113K; R_0402_1005Metric
R3, R11, R13, R23: NS/200K; R_0402_1005Metric
R4, R6, R12, R14, R17, R18, R24, R26: 100K; R_0402_1005Metric
R5, R15, R16, R25: 2K; R_0402_1005Metric
R7: 267K; R_0402_1005Metric
R8: 220K; R_0402_1005Metric
R9, R10, R19, R21, R27: 200K; R_0402_1005Metric
R20: 133.3K; R_0402_1005Metric
R22: 63.2K; R_0402_1005Metric
R28: 44.2K; R_0402_1005Metric
R34: 69.8K; R_0402_1005Metric
U1: TPS61088RHLR; IC_TPS61088RHLR; PARTREV 4219071/A 05/2017
U2, U3, U4, U5: MP214x; MP2145

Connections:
1.2V: C11.1, C12.1, C13.1, L2.2, PCI1.A1, PCI1.A2, PCI1.A3, R9.1, U2.2 (OUT)
1.5V: C22.1, C24.1, C26.1, L3.2, PCI1.A4, PCI1.A5, PCI1.A6, R19.1, U3.2 (OUT)
2.5V: C23.1, C25.1, C27.1, L4.2, PCI1.A7, PCI1.A8, R21.1, U4.2 (OUT)
3.3V: C32.1, C33.1, C34.1, L5.2, PCI1.A9, PCI1.A10, PCI1.A11, R27.1, U5.2 (OUT)
5V: C7.1, C8.1, C9.1, C14.1, C15.1, C16.1, C17.1, C18.1, C19.1, C28.1, C29.1, C30.1, C40.1, C41.1, C42.1, PCI1.B1, PCI1.B2, PCI1.B3, PCI1.B4, PCI1.B5, R3.1, R5.1, R6.1, R8.2, R11.1, R13.1, R15.1, R16.1, R17.1, R18.1, R23.1, R25.1, R26.1, U1.14 (VOUT_16), U1.15 (VOUT_14), U1.16 (VOUT_15), U2.8 (VIN), U3.8 (VIN), U4.8 (VIN), U5.8 (VIN)
BAT+: C1.1, C2.1, J1.1, J1.2, J1.3, L1.1, U1.9 (VIN)
BAT_CHG: J1.8, PCI1.B18
BAT_ISET: J1.10, PCI1.B16
BAT_PG: J1.9, PCI1.B17
GND: C1.2, C2.2, C3.2, C4.2, C5.2, C6.2, C7.2, C8.2, C9.2, C10.2, C12.2, C13.2, C14.2, C15.2, C16.2, C17.2, C18.2, C19.2, C20.2, C21.2, C24.2, C25.2, C26.2, C27.2, C28.2, C29.2, C30.2, C31.2, C33.2, C34.2, C40.2, C41.2, C42.2, D1.1 (K), D2.1 (K), D3.1 (K), D4.1 (K), J1.4, J1.5, J1.6, J1.7, J2.1, J3.1, J4.1, J6.1, J7.1, J8.1, J9.1, J10.1, J11.1, PCI1.B6, PCI1.B7, PCI1.B8, PCI1.B9, PCI1.B10, PCI1.B11, R2.2, R4.2, R10.2, R12.2, R14.2, R20.2, R22.2, R24.2, R28.2, R34.1, U1.11 (NC_11), U1.12 (NC_12), U1.20 (AGND), U1.21 (PGND), U2.10 (GND), U2.11 (GND), U2.12 (GND), U3.10 (GND), U3.11 (GND), U3.12 (GND), U4.10 (GND), U4.11 (GND), U4.12 (GND), U5.10 (GND), U5.11 (GND), U5.12 (GND)
unnamed: C3.1, R1.1, U1.18 (COMP)
unnamed: C4.1, U1.1 (VCC), U1.2 (EN)
unnamed: C5.1, R1.2
unnamed: C6.1, U1.10 (SS)
unnamed: C10.1, R3.2, R4.1, U2.6 (MODE)
unnamed: C11.2, U2.4 (Ramp)
unnamed: C20.1, R11.2, R12.1, U3.6 (MODE)
unnamed: C21.1, R13.2, R14.1, U4.6 (MODE)
unnamed: C22.2, U3.4 (Ramp)
unnamed: C23.2, U4.4 (Ramp)
unnamed: C31.1, R23.2, R24.1, U5.6 (MODE)
unnamed: C32.2, U5.4 (Ramp)
unnamed: C39.1, U1.8 (BOOT)
unnamed: C39.2, L1.2, R7.2, U1.4 (SW_7), U1.5 (SW_4), U1.6 (SW_5), U1.7 (SW_6)
unnamed: L2.1, U2.1 (SW), U2.9 (SW)
unnamed: L3.1, U3.1 (SW), U3.9 (SW)
unnamed: L4.1, U4.1 (SW), U4.9 (SW)
unnamed: L5.1, U5.1 (SW), U5.9 (SW)
unnamed: R2.1, U1.19 (ILIM)
unnamed: R6.2, U2.5 (EN)
unnamed: R7.1, U1.3 (FSW)
unnamed: R9.2, R10.1, U2.3 (FB)
unnamed: R17.2, U3.5 (EN)
unnamed: R18.2, U4.5 (EN)
unnamed: R19.2, R20.1, U3.3 (FB)
unnamed: R21.2, R22.1, U4.3 (FB)
unnamed: R26.2, U5.5 (EN)
unnamed: R27.2, R28.1, U5.3 (FB)
unnamed: R8.1, R34.2, U1.17 (FB)
PG_1.2: D1.2 (A), R5.2, U2.7 (PG)
PG_1.5: D2.2 (A), R15.2, U3.7 (PG)
PG_2.5: D3.2 (A), R16.2, U4.7 (PG)
PG_3.3: D4.2 (A), R25.2, U5.7 (PG)
REG_CHG: J1.12, PCI1.B14
REG_EN1: J1.13, PCI1.B13
REG_EN2: J1.14, PCI1.B12
REG_POWER: J1.11, PCI1.B15
